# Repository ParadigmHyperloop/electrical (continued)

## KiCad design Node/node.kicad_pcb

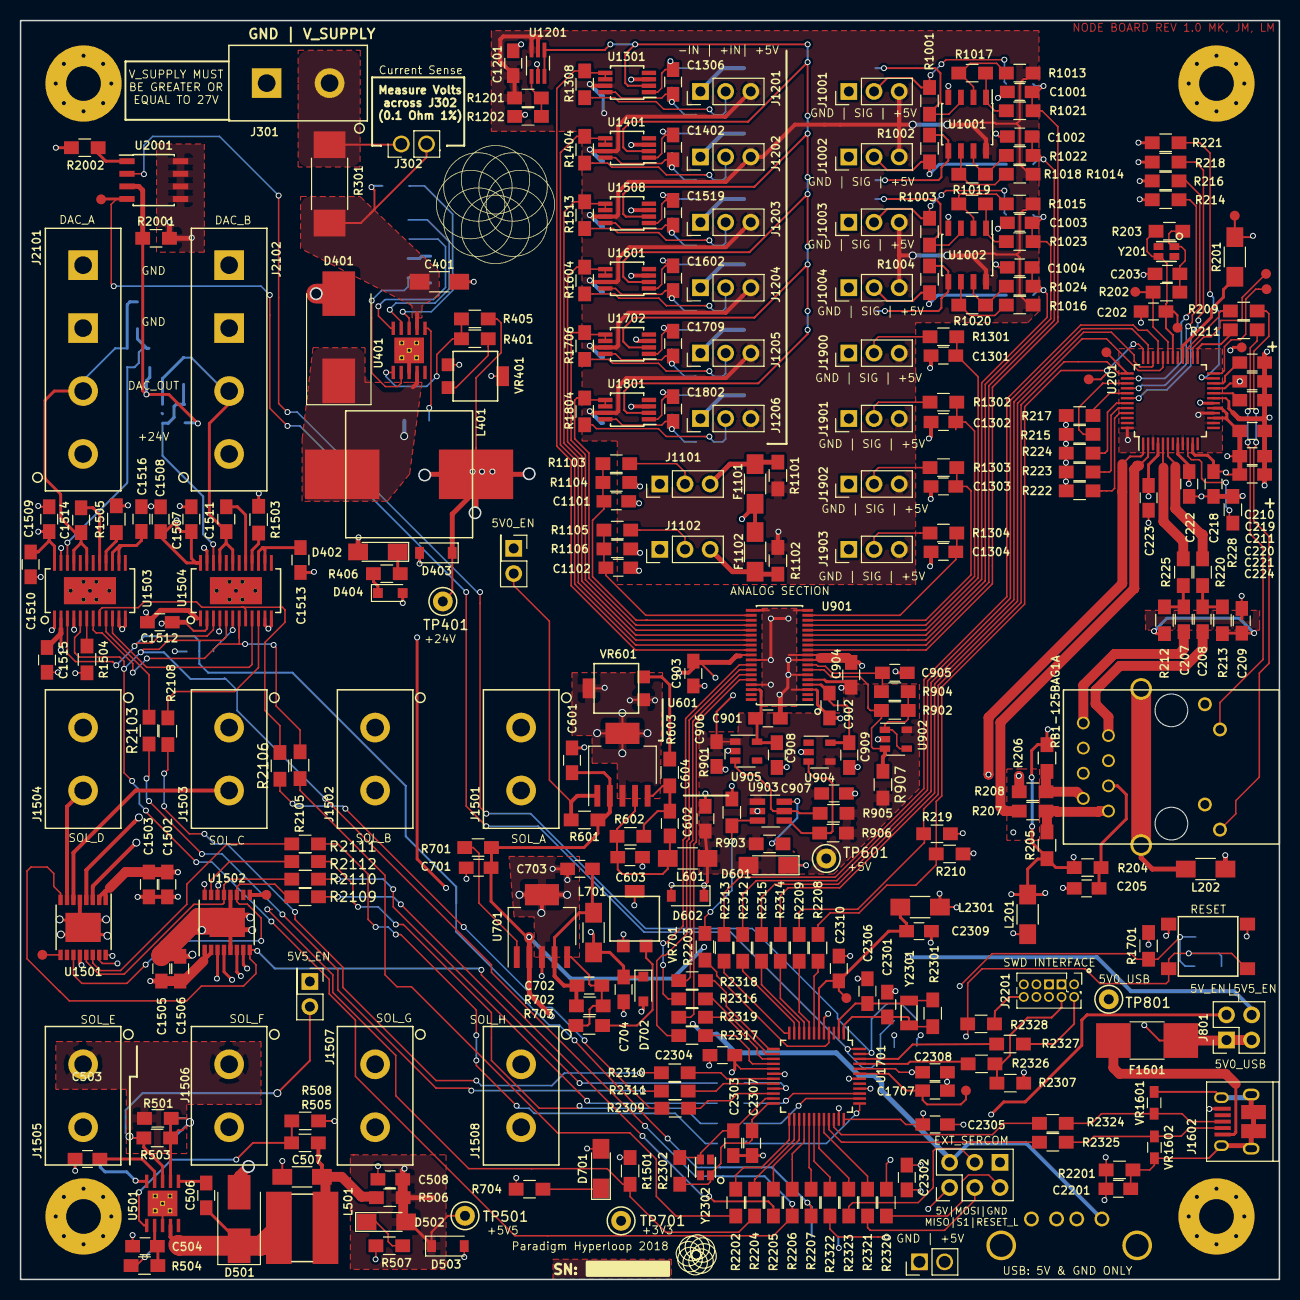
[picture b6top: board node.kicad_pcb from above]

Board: 4 copper layers, 127.0 x 127.0 mm, 399 parts (0 on the bottom side), 258 nets.

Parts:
C202, C203: 18pF; C_0805_HandSoldering
C205, C405, C506: 100nF; C_0805_HandSoldering
C207, C208: 6.8nF; C_0805_HandSoldering
C209, C210: 10nF; C_0805_HandSoldering
C211: 4.7uF; C_0805_HandSoldering
C218, C902, C2302, C2309: 10uF; C_0805_HandSoldering
C219, C220, C221, C222, C223, C224, C909, C1305, C1307, C1308, C1401, C1403, C1404, C1502, C1505, C1507, C1508, C1509, C1510, C1512, C1513, C1515, C1516, C1518, C1520, C1521, C1601, C1603, C1604, C1702, C1708, C1710, C1711, C1801, C1803, C1804, C2304, C2305, C2308, C2310: 0.1uF; C_0805_HandSoldering
C401: 2.2uF; C_1206_HandSoldering
C402, C503: 2.7nF; C_0805_HandSoldering
C403: 82pF; C_0805_HandSoldering
C404: 2.4nF; C_0805_HandSoldering
C406, C407: 22uF; C_0805_HandSoldering
C501, C502: 2.2uF; C_0805_HandSoldering
C504: 12nF; C_0805_HandSoldering
C505: 10pF; C_0805_HandSoldering
C507: 47uF; C_1206_HandSoldering
C508, C601, C603, C701, C703, C901, C903, C904, C906, C907, C908, C1201, C1306, C1402, C1519, C1602, C1707, C1709, C1802: 1uF; C_0805_HandSoldering
C602, C702, C2303, C2307: 15pF; C_0805_HandSoldering
C604, C704, C1001, C1002, C1003, C1004, C1101, C1102, C1301, C1302, C1303, C1304: C; C_0805_HandSoldering
C905: 150pF; C_0805_HandSoldering
C1503, C1506: 100uF; C_0805_HandSoldering
C1511, C1514: NOSTUFF; C_0805_HandSoldering
C2201: 4.5nF; C_0805_HandSoldering
C2301, C2306: 22pF; C_0805_HandSoldering
D401: DIODESCH; D_SMC_Handsoldering
D402, D502, D601, D701: GRN; LED_1206_HandSoldering
D403: 25V; D_SOD-123
D404: 20V; D_SOD-323_HandSoldering
D501: DIODESCH; D_SMB_Handsoldering
D503, D602: 6V; D_SOD-123
D702: 3.6V; D_SOD-323_HandSoldering
F1101, F1102: Fuse; R_1206_HandSoldering
F1601: Fuse; R_1812_HandSoldering
J201: RB1-125BAG1A; WIZNET_RB1-125BAG1A
J301, J1501, J1502, J1503, J1504, J1505, J1506, J1507, J1508: CONN_01X02; Molex_2pin_power_0010844022
J302, J303: CONN_01X02; Pin_Header_Straight_1x02_Pitch2.54mm
J801: Conn_02x02_Odd_Even; Pin_Header_Straight_2x02_Pitch2.54mm
J802, J803: Conn_02x01; Pin_Header_Straight_2x01_Pitch2.54mm
J1001, J1002, J1003, J1004, J1101, J1102, J1201, J1202, J1203, J1204, J1205, J1206, J1900, J1901, J1902, J1903: Conn_01x03; TE_3_pos_header_640456-3
J1601: Conn_02x03_Odd_Even; Pin_Header_Straight_2x03_Pitch2.54mm
J1602: USB_B_Micro; USB_Micro-B_10103594-0001LF
J2101, J2102: CONN_01X04; Molex_4pin_power_10-84-4042
J2201: Conn_02x05_Odd_Even; Pin_Header_Straight_2x05_Pitch1.27mm
L201, L202, L2301: Ferrite_Bead_Small; R_1206_HandSoldering
L401: 33uH; Wurth_inductor_7443551331
L501: 33uH; Bourns_33uH_inductor_SRR6028-330Y
L601, L701: INDUCTOR_SMALL; R_1206_HandSoldering
MK301, MK302, MK303, MK304: Mounting_Hole_PAD; MountingHole_M3x0.5_3.5mm_hole
P2101: USB_B; USB_A
R201: 0; R_1206_HandSoldering
R202, R403, R501, R506, R902, R1001, R1002, R1003, R1004, R1009, R1010, R1011, R1012, R1021, R1022, R1023, R1024, R1101, R1102, R1301, R1302, R1303, R1304, R1308, R1404, R1502, R1503, R1504, R1505, R1507, R1508, R1513, R1604, R1706, R1804, R2001, R2103, R2105, R2106, R2108, R2109, R2110, R2111, R2112, R2202, R2203, R2204, R2205, R2206, R2207, R2208, R2209, R2309, R2310, R2311, R2312, R2313, R2314, R2315, R2316, R2317, R2318, R2319, R2320, R2321, R2322, R2323, R2324, R2325, R2326, R2327, R2328, R2329, R2330, R2331, R2332: 0; R_0805_HandSoldering
R203, R1305, R1401, R1510, R1601, R1703, R1801, R2201: 1M; R_0805_HandSoldering
R204: 10; R_0805_HandSoldering
R205, R206, R212, R213: 49.9; R_0805_HandSoldering
R207, R208, R220, R225: 33; R_0805_HandSoldering
R209, R211, R704, R1702: 330; R_0805_HandSoldering
R210, R214, R215, R216, R217, R218, R219, R221, R222, R223, R224, R1701: 10K; R_0805_HandSoldering
R228: 12.4K; R_0805_HandSoldering
R301: 100m; R_2512_HandSoldering
R401: 11.5k; R_0805_HandSoldering
R402: 210k; R_0805_HandSoldering
R404: 27.4k; R_0805_HandSoldering
R405: 348k; R_0805_HandSoldering
R406: 698; R_0805_HandSoldering
R502: 124k; R_0805_HandSoldering
R503, R601, R701, R1017, R1018, R1019, R1020, R1501, R1506: 10k; R_0805_HandSoldering
R504: 17.4k; R_0805_HandSoldering
R505: 66.5k; R_0805_HandSoldering
R507: 1.4k; R_0805_HandSoldering
R508: 11.3k; R_0805_HandSoldering
R602: 93.1k; R_0805_HandSoldering
R603, R703: 29.4k; R_0805_HandSoldering
R604: 1.2k; R_0805_HandSoldering
R702: 51k; R_0805_HandSoldering
R901, R1202: 5k; R_0805_HandSoldering
R903, R905, R906: 100k; R_0805_HandSoldering
R904: 100; R_0805_HandSoldering
R907: 50K; R_0805_HandSoldering
R1005, R1006, R1007, R1008: 250; R_0805_HandSoldering
R1013, R1014, R1015, R1016: 40k; R_0805_HandSoldering
R1103, R1105: 82k; R_0805_HandSoldering
R1104, R1106: 20k; R_0805_HandSoldering
R1201: 45k; R_0805_HandSoldering
R1306, R1307, R1402, R1403, R1511, R1512, R1602, R1603, R1704, R1705, R1802, R1803, R2002: 150; R_0805_HandSoldering
R2003, R2004: 15k; R_0805_HandSoldering
R2301, R2302: NOSTUFF; R_0805_HandSoldering
R2307: 1k; R_0805_HandSoldering
SW1701: SW_Push; C&K_switch_PTS645SM43SMTR92
TP201, TP202, TP203, TP204, TP205, TP206, TP207, TP208, TP2001, TP2201, TP2301: Conn_01x01; Testpoint_circle_0.5mm
TP401, TP501, TP601, TP701, TP801: Test_Point; Test_Point_Keystone_5000-5004_Miniature
TP2101, TP2102: CONN_01X01; Testpoint_circle_0.5mm
U201: W5500; LQFP-48_7x7mm_Pitch0.5mm
U401, U501: TPS54361; TI_buckreg_TPS54361DPRR
U601, U701: TPS795; SOT-223-6
U901: ADS7953; TSSOP-38_4.4x9.7mm_Pitch0.5mm
U902: OPA192; SOT-23-5
U903: LM3880; SOT-23-6_Handsoldering
U904: LM4132; SOT-23-5
U905: TLV71333; SOT-23-5
U1001, U1002: LM358; SOIC-8_3.9x4.9mm_Pitch1.27mm
U1201: LMV601; SOT-363_SC-70-6_Handsoldering
U1301, U1401, U1508, U1601, U1702, U1801: AD849X; MSOP-8_3x3mm_Pitch0.65mm
U1501, U1502: DRV8806; TSSOP-16-1EP_4.4x5mm_Pitch0.65mm
U1503, U1504: DAC7760; HTSSOP-24_7.8x4.4mm_Pitch0.65mm_ThermalPad
U1505, U1506: OPA172; SOT-23-5
U1701: IC_MICROCHIP_SAMD21G18A-A; TQFP-48_7x7mm_Pitch0.5mm
U2001: BTS4300SGA; SOIC-8_3.9x4.9mm_Pitch1.27mm
VR401, VR601, VR701: 1k; TT_1k_potentiometer_23BR1KLFTR
VR1601, VR1602: VR; R_0603_HandSoldering
Y201, Y2302: 25MHz; Murata_25MHz_XTAL_XRCGB25M000F3M00R0
Y2301: 32.768kHz; TXC_32kHz_XTAL_9HT10-32.768KBZY-T

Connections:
3V3A_SAMD: C2309.1, C2310.1, L2301.1, TP2301.1, U1701.6
3V3A_W5500: C218.1, C219.1, C220.1, C221.1, C222.1, C223.1, C224.1, J201.L1, J201.L3, L201.2, R201.2, R204.2, R205.1, R206.1, R210.2, R219.2, TP208.1, U201.4, U201.8, U201.11, U201.15, U201.17, U201.21
+3V3: C704.1, C1512.2, C1515.2, C2302.1, C2304.1, C2305.1, C2308.1, D701.2, D702.1, J2201.1, L201.1, L701.2, L2301.2, R1501.1, R1506.1, R1701.2, R2003.1, R2004.1, R2307.2, TP701.1, U1503.2, U1504.2, U1701.17, U1701.36, U1701.44
+5V: C604.1, C903.1, C904.1, C906.1, C907.1, C1201.2, C1308.2, C1404.2, C1521.2, C1604.2, C1711.2, C1804.2, D601.2, D602.1, J303.2, J801.2, J1001.3, J1002.3, J1003.3, J1004.3, J1201.3, J1202.3, J1203.3, J1204.3, J1205.3, J1206.3, J1601.2, J1900.3, J1901.3, J1902.3, J1903.3, L601.2, P2101.1, R903.1, R905.1, R906.1, R907.1, R1013.2, R1014.2, R1015.2, R1016.2, R1101.1, R1102.1, R1201.1, TP601.1, U901.5, U901.29, U902.5, U903.1, U904.4, U905.1, U1001.8, U1002.8, U1201.5, U1201.6, U1301.7, U1401.7, U1508.7, U1601.7, U1702.7, U1801.7
+24V: C406.1, C407.1, C1502.2, C1503.2, C1505.2, C1506.2, D402.2, D403.1, F1101.1, F1102.1, J1501.1, J1502.1, J1503.1, J1504.1, J1505.1, J1506.1, J1507.1, J1508.1, J2101.1, J2102.1, L401.2, R405.1, R501.2, R2001.2, TP401.1, U1501.1, U1501.2, U1502.1, U1502.2, U2001.5, U2001.6, U2001.7, U2001.8
/Actuator Interface/24V0_DAC: C1507.2, C1508.2, C1509.2, C1510.2, R2001.1, U1503.24, U1504.24, U1505.5, U1506.5, U2001.3
/Actuator Interface/DAC1_CLR_SEL: R1504.2, U1503.6
/Actuator Interface/DAC1_DATAIN: R2103.2, U1503.9
/Actuator Interface/DAC1_DATAOUT: U1503.10, U1504.9
/Actuator Interface/DAC1_DVDD_EN_L: R1505.2, U1503.16
/Actuator Interface/DAC1_VIOUT: C1514.1, J2101.2, R1508.1, U1503.19, U1503.21, U1505.3
/Actuator Interface/DAC1_VREF: C1516.2, U1503.14, U1503.15
/Actuator Interface/DAC1_VSENSE+: R1508.2, U1503.22, U1505.1, U1505.4
/Actuator Interface/DAC2_CLR_SEL: R1502.2, U1504.6
/Actuator Interface/DAC2_DATAOUT: R2108.2, U1504.10
/Actuator Interface/DAC2_DVDD_EN_L: R1503.2, U1504.16
/Actuator Interface/DAC2_VIOUT: C1511.1, J2102.2, R1507.1, U1504.19, U1504.21, U1506.3
/Actuator Interface/DAC2_VREF: C1513.2, U1504.14, U1504.15
/Actuator Interface/DAC2_VSENSE+: R1507.2, U1504.22, U1506.1, U1506.4
/Actuator Interface/DAC_ALARM_L: R1506.2, R2207.2, U1503.3, U1504.3
/Actuator Interface/DAC_CLR: R2206.2, U1503.5, U1504.5
/Actuator Interface/DAC_CS: R2105.2, U1503.7, U1504.7
/Actuator Interface/DAC_SCLK: R2106.2, U1503.8, U1504.8
/Actuator Interface/Q0: R2109.1, R2109.2, R2329.2, U1501.11, U1502.11
/Actuator Interface/Q1: R2110.1, R2330.2
/Actuator Interface/Q2: R2111.1, R2331.2
/Actuator Interface/Q3: R2112.1, R2332.2
/Actuator Interface/SOL1_DATAIN: R2111.2, U1501.14
/Actuator Interface/SOL1_DATAOUT: U1501.15, U1502.14
/Actuator Interface/SOL1_OUT1: J1501.2, U1501.3
/Actuator Interface/SOL1_OUT2: J1502.2, U1501.4
/Actuator Interface/SOL1_OUT3: J1503.2, U1501.6
/Actuator Interface/SOL1_OUT4: J1504.2, U1501.7
/Actuator Interface/SOL1_RST: TP2102.1, U1501.9
/Actuator Interface/SOL2_DATAOUT: R2112.2, U1502.15
/Actuator Interface/SOL2_OUT1: J1505.2, U1502.3
/Actuator Interface/SOL2_OUT2: J1506.2, U1502.4
/Actuator Interface/SOL2_OUT3: J1507.2, U1502.6
/Actuator Interface/SOL2_OUT4: J1508.2, U1502.7
/Actuator Interface/SOL2_RST: TP2101.1, U1502.9
/Actuator Interface/SOL_DAC_C0: R1501.2, R2204.2, U1501.16, U1502.16
/Actuator Interface/SOL_DAC_C1: R2205.2, U1501.8, U1502.8
/Actuator Interface/SOL_DAC_CS2: R2105.1, R2202.2
/Actuator Interface/SOL_DAC_MISO: R2108.1, R2310.2
/Actuator Interface/SOL_DAC_MOSI: R2103.1, R2311.2
/Actuator Interface/SOL_DAC_S1: R2106.1, R2309.2
/Actuator Interface/SOL_SCLK: R2110.2, U1501.13, U1502.13
/Microcontroller/ADC_CS: R2316.2, U901.31
/Microcontroller/ADC_MISO: R2318.2, U901.33
/Microcontroller/ADC_MOSI: R2319.2, U901.34
/Microcontroller/ADC_S1: R2317.2, U901.32
/Microcontroller/EXT_RESET_L: R1702.2, R2320.1, R2328.1, SW1701.2
/Microcontroller/ISP_MISO: J1601.1, R2322.2
/Microcontroller/ISP_MOSI: J1601.4, R2323.2
/Microcontroller/ISP_RESET_L: J1601.5, R2320.2
/Microcontroller/ISP_S1: J1601.3, R2321.2
/Microcontroller/NETW_C0: R210.1, R2208.2, TP205.1, U201.36
/Microcontroller/NETW_C1: R219.1, R2209.2, TP204.1, U201.37
/Microcontroller/NETW_CS: R2314.2, U201.32
/Microcontroller/NETW_MISO: R2315.2, U201.34
/Microcontroller/NETW_MOSI: R2312.2, U201.35
/Microcontroller/NETW_S1: R2313.2, U201.33
/Microcontroller/PA03: R2203.1, U1701.4
/Microcontroller/PA04: R2314.1, U1701.9
/Microcontroller/PA05: R2315.1, U1701.10
/Microcontroller/PA06: R2312.1, U1701.11
/Microcontroller/PA07: R2313.1, U1701.12
/Microcontroller/PA08: R2318.1, U1701.13
/Microcontroller/PA09: R2316.1, U1701.14
/Microcontroller/PA10: R2319.1, U1701.15
/Microcontroller/PA11: R2317.1, U1701.16
/Microcontroller/PA12: R2329.1, U1701.21
/Microcontroller/PA13: R2309.1, U1701.22
/Microcontroller/PA14: C2303.1, R2302.2, U1701.23, Y2302.2
/Microcontroller/PA15: C2307.1, R2302.1, U1701.24, Y2302.1
/Microcontroller/PA16: R2202.1, U1701.25
/Microcontroller/PA17: R2204.1, U1701.26
/Microcontroller/PA18: R2205.1, U1701.27
/Microcontroller/PA19: R2206.1, U1701.28
/Microcontroller/PA20: R2207.1, U1701.29
/Microcontroller/PA21: R2322.1, U1701.30
/Microcontroller/PA22: R2323.1, U1701.31
/Microcontroller/PA23: R2321.1, U1701.32
/Microcontroller/PA27: R2330.1, U1701.39
/Microcontroller/PA30: R2326.1, U1701.45
/Microcontroller/PA31: R2327.1, U1701.46
/Microcontroller/PB02: R2003.2, U1701.47, U2001.2
/Microcontroller/PB03: R2004.2, TP2001.1, U1701.48, U2001.4
/Microcontroller/PB08: R2208.1, U1701.7
/Microcontroller/PB09: R2209.1, U1701.8
/Microcontroller/PB10: R2310.1, U1701.19
/Microcontroller/PB11: R2311.1, U1701.20
/Microcontroller/PB12: R2331.1, U1701.37
/Microcontroller/PB13: R2332.1, U1701.38
/Microcontroller/RESET_L: C1702.1, R1701.1, R1702.1, U1701.40
/Microcontroller/SWDCLK: J2201.4, R2307.1, R2326.2
/Microcontroller/SWDIO: J2201.2, R2327.2
/Microcontroller/SWD_RESET_L: J2201.10, R2328.2
/Microcontroller/USB_D+: J1602.3, R2324.2, VR1601.1
/Microcontroller/USB_D-: J1602.2, R2325.2, VR1602.1
/Microcontroller/USB_R_D+: R2324.1, U1701.34
/Microcontroller/USB_R_D-: R2325.1, U1701.33
/Microcontroller/VDDCORE_1V2: C1707.2, TP2201.1, U1701.43
/Microcontroller/XTAL32K_IN: C2301.1, R2301.2, U1701.1, Y2301.1
/Microcontroller/XTAL32K_OUT: C2306.1, R2301.1, U1701.2, Y2301.2
/Network_Interface/1V2_VBG_NC: TP207.1, U201.18
/Network_Interface/1V20: C210.1, U201.22
/Network_Interface/3V3D_W5500: R201.1, U201.28
/Network_Interface/ACT_LED: R209.2, U201.27
/Network_Interface/ACT_LED_R: J201.L4, R209.1
/Network_Interface/DUP_LED_NC: TP201.1, U201.26
/Network_Interface/LINK_LED: R211.1, U201.25
/Network_Interface/LINK_LED_R: J201.L2, R211.2
/Network_Interface/PMODE0: R222.2, U201.45
/Network_Interface/PMODE1: R223.2, U201.44
/Network_Interface/PMODE2: R224.2, U201.43
/Network_Interface/REF_CAP: C211.1, U201.20
/Network_Interface/REF_RES: R228.2, U201.10
/Network_Interface/RSVD0: R221.2, U201.23
/Network_Interface/RSVD1: R214.1, U201.38
/Network_Interface/RSVD2: R215.1, U201.39
/Network_Interface/RSVD3: R216.1, U201.40
/Network_Interface/RSVD4: R217.1, U201.41
/Network_Interface/RSVD5: R218.1, U201.42
/Network_Interface/RX_C_N: C207.2, J201.R8
/Network_Interface/RX_C_P: C208.2, J201.R7
/Network_Interface/RX_N: R225.2, U201.5
/Network_Interface/RX_P: R220.2, U201.6
/Network_Interface/SPD_LED_NC: TP206.1, U201.24
/Network_Interface/TCT_RCT: C205.1, J201.R3, R204.1
/Network_Interface/TX_N: R208.2, U201.1
/Network_Interface/TX_P: R207.2, U201.2
/Network_Interface/TX_R_N: J201.R2, R206.2, R208.1
/Network_Interface/TX_R_P: J201.R1, R205.2, R207.1
/Network_Interface/XTAL_IN: C202.2, R203.2, TP203.1, U201.30, Y201.2
/Network_Interface/XTAL_OUT: R202.2, TP202.1, U201.31
/Power/3.3V (Clean) Supply/3V3_UNFILT: C702.1, C703.1, L701.1, R702.1, U701.4
/Power/3.3V (Clean) Supply/5V5: C508.1, C601.1, C701.1, D502.2, D503.1, J801.4, R506.1, R601.1, R701.1, TP501.1, U601.2, U701.2
/Power/5.5V (Noisy) Supply/5V5_UNFILT: C507.1, L501.2, R505.1, R506.2
/Power/5.5V (Noisy) Supply/24V0_R: C501.1, C502.1, R501.1, R503.2, U501.2
/Power/5.5V (Noisy) Supply/COMP: C504.1, R504.1, U501.7
/Power/5.5V (Noisy) Supply/ENABLE: J803.2, R503.1, U501.3
/Power/5.5V (Noisy) Supply/FB: R505.2, R508.1, U501.6
/Power/5.5V (Noisy) Supply/RT: R502.1, U501.5
/Power/5.5V (Noisy) Supply/SS: C503.1, U501.4
/Power/5.5V (Noisy) Supply/SW: C506.1, D501.1, L501.1, U501.9
/Power/5V0_USB: F1601.2, J801.1, J801.3, TP801.1
/Power/5V (Clean) Supply/5V0_UNFILT: C602.1, C603.1, L601.1, R602.1, U601.4
/Power/5V (Clean) Supply/ENABLE: J802.2, R601.2, U601.1
/Power/ISENSE_N: C401.1, J302.2, R301.1, R403.2, U401.2
/Power/ISENSE_P: J301.1, J302.1, R301.2
/Power/Motor Supply/COMP: C403.1, R404.1, U401.7
/Power/Motor Supply/EN: R403.1, U401.3
/Power/Motor Supply/FB: R401.1, R405.2, U401.6
/Power/Motor Supply/RT: R402.1, U401.5
/Power/Motor Supply/SS: C402.1, U401.4
/Power/Motor Supply/SW: C405.1, D401.1, L401.1, U401.9
/Sensors/ADC/3V3_EN: R905.2, U903.5, U905.3
/Sensors/ADC/ADC_CH0: R1308.1, U901.28, U1301.5, U1301.6
/Sensors/ADC/ADC_CH1: R1404.1, U901.27, U1401.5, U1401.6
/Sensors/ADC/ADC_CH2: R1513.1, U901.26, U1508.5, U1508.6
/Sensors/ADC/ADC_CH3: R1604.1, U901.25, U1601.5, U1601.6
/Sensors/ADC/ADC_CH4: R1706.1, U901.24, U1702.5, U1702.6
/Sensors/ADC/ADC_CH5: R1804.1, U901.23, U1801.5, U1801.6
/Sensors/ADC/ADC_CH6: C1101.1, R1103.2, R1104.1, U901.22
/Sensors/ADC/ADC_CH7: C1102.1, R1105.2, R1106.1, U901.21
/Sensors/ADC/ADC_CH8: C1304.1, R1304.1, U901.18
/Sensors/ADC/ADC_CH9: C1303.1, R1303.1, U901.17
/Sensors/ADC/ADC_CH10: C1302.1, R1302.1, U901.16
/Sensors/ADC/ADC_CH11: C1301.1, R1301.1, U901.15
/Sensors/ADC/ADC_CH12: C1004.1, R1012.1, R1024.1, U901.14
/Sensors/ADC/ADC_CH13: C1003.1, R1011.1, R1023.1, U901.13
/Sensors/ADC/ADC_CH14: C1002.1, R1010.1, R1022.1, U901.12
/Sensors/ADC/ADC_CH15: C1001.1, R1009.1, R1021.1, U901.11
/Sensors/ADC/AINP: C905.1, R904.1, U901.8
/Sensors/ADC/MXO: R902.1, R907.2, U901.7, U902.3
/Sensors/ADC/POWER_SEQ_ADC: R901.1, R2203.2, U903.3
/Sensors/ADC/TC_to_Volt/tc_to_v_0/+IN: J1201.2, R1307.2, R1308.2
/Sensors/ADC/TC_to_Volt/tc_to_v_0/-IN: J1201.1, R1305.2, R1306.2
/Sensors/ADC/TC_to_Volt/tc_to_v_1/+IN: J1202.2, R1403.2, R1404.2
/Sensors/ADC/TC_to_Volt/tc_to_v_1/-IN: J1202.1, R1401.2, R1402.2
/Sensors/ADC/TC_to_Volt/tc_to_v_2/+IN: J1203.2, R1512.2, R1513.2
/Sensors/ADC/TC_to_Volt/tc_to_v_2/-IN: J1203.1, R1510.2, R1511.2
/Sensors/ADC/TC_to_Volt/tc_to_v_3/+IN: J1204.2, R1603.2, R1604.2
/Sensors/ADC/TC_to_Volt/tc_to_v_3/-IN: J1204.1, R1601.2, R1602.2
/Sensors/ADC/TC_to_Volt/tc_to_v_4/+IN: J1205.2, R1705.2, R1706.2
/Sensors/ADC/TC_to_Volt/tc_to_v_4/-IN: J1205.1, R1703.2, R1704.2
/Sensors/ADC/TC_to_Volt/tc_to_v_5/+IN: J1206.2, R1803.2, R1804.2
/Sensors/ADC/TC_to_Volt/tc_to_v_5/-IN: J1206.1, R1801.2, R1802.2
/Sensors/ADC/TC_to_Volt/tc_vref: U1201.3, U1201.4, U1301.2, U1401.2, U1508.2, U1601.2, U1702.2, U1801.2
/Sensors/ADC/VREF_EN: R906.2, U903.4, U904.3
/USB Interface/USB_SHLD: C2201.1, J1602.6, R2201.1, VR1601.2, VR1602.2
ADC_2V5_REF: C902.1, C909.2, U901.4, U904.5
ADC_3V3: C901.1, C908.1, U901.36, U905.5
GND: C202.1, C203.1, C205.2, C209.2, C210.2, C211.2, C218.2, C219.2, C220.2, C221.2, C222.2, C223.2, C224.2, C401.2, C402.2, C403.2, C404.2, C406.2, C407.2, C501.2, C502.2, C503.2, C504.2, C505.2, C507.2, C508.2, C601.2, C603.2, C604.2, C701.2, C703.2, C704.2, C901.2, C902.2, C903.2, C904.2, C905.2, C906.2, C907.2, C908.2, C909.1, C1001.2, C1002.2, C1003.2, C1004.2, C1101.2, C1102.2, C1201.1, C1301.2, C1302.2, C1303.2, C1304.2, C1305.1, C1307.2, C1308.1, C1401.1, C1403.2, C1404.1, C1502.1, C1503.1, C1505.1, C1506.1, C1507.1, C1508.1, C1509.1, C1510.1, C1512.1, C1513.1, C1515.1, C1516.1, C1518.1, C1520.2, C1521.1, C1601.1, C1603.2, C1604.1, C1702.2, C1707.1, C1708.1, C1710.2, C1711.1, C1801.1, C1803.2, C1804.1, C2201.2, C2301.2, C2302.2, C2303.2, C2304.2, C2305.2, C2306.2, C2307.2, C2308.2, C2309.2, C2310.2, D401.2, D403.2, D404.2, D501.2, D503.2, D602.2, D702.2, J301.2, J303.1, J802.1, J803.1, J1001.1, J1002.1, J1003.1, J1004.1, J1101.1, J1102.1, J1601.6, J1602.5, J1900.1, J1901.1, J1902.1, J1903.1, J2101.3, J2101.4, J2102.3, J2102.4, J2201.3, J2201.5, L202.1, MK301.1, MK302.1, MK303.1, MK304.1, P2101.4, P2101.5, R214.2, R215.2, R216.2, R217.2, R218.2, R221.1, R222.1, R223.1, R224.1, R228.1, R402.2, R502.2, R507.2, R508.2, R604.2, R704.2, R901.2, R1005.2, R1006.2, R1007.2, R1008.2, R1104.2, R1106.2, R1202.2, R1305.1, R1401.1, R1502.1, R1503.1, R1504.1, R1505.1, R1510.1, R1601.1, R1703.1, R1801.1, R2002.2, R2201.2, SW1701.1, U201.3, U201.9, U201.14, U201.16, U201.19, U201.29, U201.48, U401.8, U401.11, U501.8, U501.11, U601.3, U601.6, U701.3, U701.6, U901.3, U901.6, U901.9, U901.10, U901.19, U901.20, U901.30, U901.35, U902.2, U903.2, U904.2, U905.2, U1001.4, U1002.4, U1201.2, U1301.3, U1401.3, U1501.5, U1501.12, U1501.17, U1502.5, U1502.12, U1502.17, U1503.1, U1503.4, U1503.11, U1503.12, U1503.23, U1504.1, U1504.4, U1504.11, U1504.12, U1504.23, U1505.2, U1506.2, U1508.3, U1601.3, U1701.5, U1701.18, U1701.35, U1701.42, U1702.3, U1801.3, VR401.2, VR401.3, VR601.2, VR601.3, VR701.2, VR701.3
unnamed: C203.2, R202.1, R203.1, Y201.1
unnamed: C207.1, R212.1, R225.1
unnamed: C208.1, R213.1, R220.1
unnamed: C209.1, R212.2, R213.2
unnamed: C404.1, R404.2
unnamed: C405.2, U401.1
unnamed: C505.1, R504.2
unnamed: C506.2, U501.1
unnamed: C602.2, R602.2, R603.1, U601.5
unnamed: C702.2, R702.2, R703.1, U701.5
unnamed: C1305.2, C1306.2, R1306.1, U1301.1
unnamed: C1306.1, C1307.1, R1307.1, U1301.8
unnamed: C1401.2, C1402.2, R1402.1, U1401.1
unnamed: C1402.1, C1403.1, R1403.1, U1401.8
unnamed: C1511.2, U1504.17
unnamed: C1514.2, U1503.17
unnamed: C1518.2, C1519.2, R1511.1, U1508.1
unnamed: C1519.1, C1520.1, R1512.1, U1508.8
unnamed: C1601.2, C1602.2, R1602.1, U1601.1
unnamed: C1602.1, C1603.1, R1603.1, U1601.8
unnamed: C1708.2, C1709.2, R1704.1, U1702.1
unnamed: C1709.1, C1710.1, R1705.1, U1702.8
unnamed: C1801.2, C1802.2, R1802.1, U1801.1
unnamed: C1802.1, C1803.1, R1803.1, U1801.8
unnamed: D402.1, R406.1
unnamed: D404.1, R406.2
unnamed: D502.1, R507.1
unnamed: D601.1, R604.1
unnamed: D701.1, R704.1
unnamed: F1101.2, J1101.3, R1101.2
unnamed: F1102.2, J1102.3, R1102.2
unnamed: F1601.1, J1602.1
unnamed: J201.SH, L202.2
unnamed: J1001.2, R1001.2, R1009.2
unnamed: J1002.2, R1002.2, R1010.2
unnamed: J1003.2, R1003.2, R1011.2
unnamed: J1004.2, R1004.2, R1012.2
unnamed: J1101.2, R1103.1
unnamed: J1102.2, R1105.1
unnamed: J1900.2, R1301.2
unnamed: J1901.2, R1302.2
unnamed: J1902.2, R1303.2
unnamed: J1903.2, R1304.2
unnamed: R401.2, VR401.1
unnamed: R603.2, VR601.1
unnamed: R701.2, U701.1
unnamed: R703.2, VR701.1
unnamed: R902.2, R904.2, U902.1, U902.4
unnamed: R903.2, U903.6
unnamed: R1001.1, R1005.1, U1001.3
unnamed: R1002.1, R1006.1, U1001.5
unnamed: R1003.1, R1007.1, U1002.3
unnamed: R1004.1, R1008.1, U1002.5
unnamed: R1013.1, R1017.2, U1001.2
unnamed: R1014.1, R1018.2, U1001.6
unnamed: R1015.1, R1019.2, U1002.2
unnamed: R1016.1, R1020.2, U1002.6
unnamed: R1017.1, R1021.2, U1001.1
unnamed: R1018.1, R1022.2, U1001.7
unnamed: R1019.1, R1023.2, U1002.1
unnamed: R1020.1, R1024.2, U1002.7
unnamed: R1201.2, R1202.1, U1201.1
unnamed: R2002.1, U2001.1

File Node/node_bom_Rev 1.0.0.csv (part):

Component,Description,Part,References,Value,Footprint,Quantity Per PCB,Datasheet,Digikey P/N,Mfg. Part Num,Vendor Part Num,Vendor Name,Mfg. Name,Vendor,Vendor P/N,MFG. P/N,Manufacturer,Package,MP,Stuffing,Tolerance,Manufacturer P/N,Mfr P/N
1,,C_small,C909 C1502 C1505 C1507 C1508 C1509 C1510 C1512 C1513 C1515 C1516,0.1uF,C_0805_HandSoldering,11,,,,,,,,,,,,,,,,
2,,C,C205 C219 C220 C221 C222 C223 C224 C1305 C1307 C1308 C1401 C1403 C1404 C1518 C1520 C1521 C1601 C1603 C1604 C1702 C1708 C1710 C1711 C1801 C1803 C1804 C2304 C2305 C2308 C2310,100nF,C_0805_HandSoldering,30,,311-1088-1-ND,,,,,,,,,,,,,,
3,,C_large,C405 C506,100nF,C_0805_HandSoldering,2,,,GMK212BJ104KGHT,587-3364-1-ND,Digi-Key,Taiyo Yuden,,,,,,,,,,
4,,C_small,C1503 C1506,100uF,C_0805_HandSoldering,2,,,,,,,,,,,,,,,,
5,,C,C209 C210,10nF,C_0805_HandSoldering,2,,,,,,,,,,,,,,,,
6,,C_large,C505,10pF,C_0805_HandSoldering,1,,,C0805C100K5GACTU,399-7975-1-ND,Digi-Key,Kemet,,,,,,,,,,
7,,C,C218 C2302 C2309,10uF,C_0805_HandSoldering,3,,,,,,,,,,,,,,,,
8,,C_small,C902,10uF,C_0805_HandSoldering,1,,,,,,,,,,,,,,,,
9,,C_large,C504,12nF,C_0805_HandSoldering,1,,,CL21B123KBANNNC,1276-2454-1-ND,Digi-Key,Samsung,,,,,,,,,,
10,,C_small,C905,150pF,C_0805_HandSoldering,1,,,,,,,,,,,,,,,,
11,,C,C2303 C2307,15pF,C_0805_HandSoldering,2,,,,,,,,,,,,,,,,
12,,C_large,C602 C702,15pF,C_0805_HandSoldering,2,,,CC0805JRNPO9BN150,311-1101-1-ND,Digi-Key,Yageo,,,,,,,,,,
13,,C,C202 C203,18pF,C_0805_HandSoldering,2,,,,,,,,,,,,,,,,
14,,C,C1201 C1306 C1402 C1519 C1602 C1707 C1709 C1802,1uF,C_0805_HandSoldering,8,,1276-1946-1-ND,,,,,,,,,,,,,,
15,,C_large,C508 C601 C603 C701 C703,1uF,C_0805_HandSoldering,5,,,GRT21BC81E105KE13L CC0805KRX5R7BB105,490-12351-1-ND 311-3427-1-ND,Digi-Key,Murata Yageo,,,,,,,,,,
16,,C_small,C901 C903 C904 C906 C907 C908,1uF,C_0805_HandSoldering,6,,,,,,,,,,,,,,,,
17,,C_large,C401,2.2uF,C_1206_HandSoldering,1,,,C3216X7S2A225K160AB,445-5207-1-ND,Digi-Key,TDK,,,,,,,,,,
18,,C_large,C501 C502,2.2uF,C_0805_HandSoldering,2,,,C2012X7R1H225K125AC,445-5968-1-ND,Digi-Key,TDK,,,,,,,,,,
19,,C_large,C404,2.4nF,C_0805_HandSoldering,1,,,GRM2165C1H242JA01D,490-1629-1-ND,Digi-Key,Murata,,,,,,,,,,
20,,C_large,C402 C503,2.7nF,C_0805_HandSoldering,2,,,CC0805KRX7R9BB272,311-1130-1-ND,Digi-Key,Yageo,,,,,,,,,,
21,,C,C2301 C2306,22pF,C_0805_HandSoldering,2,,,,,,,,,,,,,,,,
22,,C_large,C406 C407,22uF,C_0805_HandSoldering,2,,,C2012X5R1V226M125AC,445-14428-1-ND,Digi-Key,TDK,,,,,,,,,,
23,,C,C2201,4.5nF,C_0805_HandSoldering,1,,,,,,,,,,,,,,,,
24,,C,C211,4.7uF,C_0805_HandSoldering,1,,,,,,,,,,,,,,,,
25,,C_large,C507,47uF,C_1206_HandSoldering,1,,,CL31A476MPHNNNE,1276-3063-1-ND,Digi-Key,Samsung,,,,,,,,,,
26,,C,C207 C208,6.8nF,C_0805_HandSoldering,2,,,,,,,,,,,,,,,,
27,,C_large,C403,82pF,C_0805_HandSoldering,1,,,CL21C820JB61PNC,1276-2695-1-ND,Digi-Key,Samsung,,,,,,,,,,
28,,C,C1001 C1002 C1003 C1004 C1101 C1102 C1301 C1302 C1303 C1304,C,C_0805_HandSoldering,10,,,,,,,,,,,,,,,,
29,,C_large,C604 C704,C,C_0805_HandSoldering,2,,,,,,,,,,,,,,,,
30,,D_Zener_ALT,D404,20V,D_SOD-323_HandSoldering,1,,,MM3Z20VT1G,MM3Z20VT1GOSCT-ND,,ON Semi,,,,,,,,,,
31,,D_Zener_ALT,D403,25V,D_SOD-123,1,,,MMSZ4710T1G,MMSZ4710T1GOSCT-ND,Digi-Key,ON Semi,,,,,,,,,,
32,,D_Zener_ALT,D702,3.6V,D_SOD-323_HandSoldering,1,,,MM3Z3V6T1G,MM3Z3V6T1GOSCT-ND,Digi-Key,ON Semi,,,,,,,,,,
33,,D_Zener_ALT,D503 D602,6V,D_SOD-123,2,,,MMSZ5233B-TP,MMSZ5233B-TPMSCT-ND,Digi-Key,Micro,,,,,,,,,,
34,,DIODESCH,D401,DIODESCH,D_SMC_Handsoldering,1,,,B560C-13-F,B560C-FDICT-ND,Digi-Key,Diodes,,,,,,,,,,
35,,DIODESCH,D501,DIODESCH,D_SMB_Handsoldering,1,,,B140B-13-F,B140B-FDICT-ND,Digi-Key,Diodes,,,,,,,,,,
36,,LED,D402 D502 D601 D701,GRN,LED_1206_HandSoldering,4,,,APT3216LZGCK,754-1944-1-ND,Digi-Key,Kingbright,,,,,,,,,,
37,,Fuse,F1101 F1102,Fuse,R_1206_HandSoldering,2,,,C1Q 250,507-1073-1-ND,,Bel Fuse,,,,,,,,,,
38,,Fuse,F1601,Fuse,R_1812_HandSoldering,1,,,MF-MSMF050-2CT-ND,MF-MSMF050-2,,Bourns,,,,,,,,,,
39,"Generic connector, single row, 01x02",Conn_01x02,J301 J1501 J1502 J1503 J1504 J1505 J1506 J1507 J1508,CONN_01X02,Molex_2pin_power_0010844022,9,,,,,,,DigiKey,WM1263-ND,0010844022,"Molex, LLC Molex LLC",,,,,,
40,"Generic connector, single row, 01x02",Conn_01x02,J302 J303,CONN_01X02,Pin_Header_Straight_1x02_Pitch2.54mm,2,,,,,,,DigiKey,S7000-ND,PPTC021LFBN-RC,Sullins Conn. Solutions,,,,,,
41,"Generic connector, single row, 01x04",Conn_01x04,J1509 J1510,CONN_01X04,Molex_4pin_power_10-84-4042,2,,,,,,,DigiKey,WM1265-ND,10-84-4042,Molex Connector Corporation,,,,,,
42,"Generic connector, single row, 01x03",Conn_01x03,J1001 J1002 J1003 J1004 J1101 J1102 J1201 J1202 J1203 J1204 J1205 J1206 J1900 J1901 J1902 J1903,Conn_01x03,TE_3_pos_header_640456-3,16,,,640456-3,A19470-ND,,TE Connectivity,,,,,,,,,,
43,"Generic connector, double row, 02x01, this symbol is compatible with counter-clockwise, top-bottom and odd-even numbering schemes.",Conn_02x01,J802 J803,Conn_02x01,Pin_Header_Straight_2x01_Pitch2.54mm,2,,,,,,,DigiKey,952-2262-ND,M20-9990246,Harwin Inc,,,,,,
44,"Generic connector, double row, 02x02, odd/even pin numbering scheme (row 1 odd numbers, row 2 even numbers)",Conn_02x02_Odd_Even,J801,Conn_02x02_Odd_Even,Pin_Header_Straight_2x02_Pitch2.54mm,1,,,,,,,DigiKey,609-3242-ND,67997-404HLF,Amphenol FCI,,,,,,
45,"Generic connector, double row, 02x03, odd/even pin numbering scheme (row 1 odd numbers, row 2 even numbers)",Conn_02x03_Odd_Even,J1601,Conn_02x03_Odd_Even,Pin_Header_Straight_2x03_Pitch2.54mm,1,,,,,,,DigiKey,S9015E-03-ND,GRPB032VWVN-RC,Sullins Conn. Solutions,,,,,,
46,"Generic connector, double row, 02x05, odd/even pin numbering scheme (row 1 odd numbers, row 2 even numbers)",Conn_02x05_Odd_Even,J2201,Conn_02x05_Odd_Even,Pin_Header_Straight_2x05_Pitch1.27mm,1,,,,,,,DigiKey,609-3712-ND,20021111-00010T4LF,Amphenol FCI,,,,,,
47,,RB1-125BAG1A,J201,RB1-125BAG1A,WIZNET_RB1-125BAG1A,1,2.18 USD,,RB1-125BAG1A,,,WIZnet,,,,,HVQFN-36 NXP Semiconductors,RB1-125BAG1A,,,,
48,USB Micro Type B connector,USB_B_Micro,J1602,USB_B_Micro,USB_Micro-B_10103594-0001LF,1,,,609-4050-1-ND,10103594-0001LF,,Amphenol,,,,,,,,,,
49,,L_large,L401,33uH,Wurth_inductor_7443551331,1,,,7443551331,732-3881-1-ND,Digi-Key,Wurth Electronics,,,,,,,,,,
50,,L_large,L501,33uH,Bourns_33uH_inductor_SRR6028-330Y,1,,,SRR6028-330Y,SRR6028-330YCT-ND,Digi-Key,Bourns,,,,,,,,,,
51,,Ferrite_Bead_Small,L201 L202 L2301,Ferrite_Bead_Small,R_1206_HandSoldering,3,,,,,,,,,,,,,,,,
52,,L_small,L601 L701,INDUCTOR_SMALL,R_1206_HandSoldering,2,,,RC1206JR-070RL,311-0.0ERCT-ND,,Yageo,,,,,,,,,,
53,,R,R202 R1001 R1002 R1003 R1004 R1009 R1010 R1011 R1012 R1021 R1022 R1023 R1024 R1101 R1102 R1301 R1302 R1303 R1304 R1308 R1404 R1513 R1604 R1706 R1804 R2202 R2203 R2204 R2205 R2206 R2207 R2208 R2209 R2308 R2309 R2310 R2311 R2312 R2313 R2314 R2315 R2316 R2317 R2318 R2319 R2320 R2321 R2322 R2323 R2324 R2325 R2326 R2327 R2328,0,R_0805_HandSoldering,54,,,,,,,,,,,,,,,,
54,,R_large,R403 R501 R506 R1502 R1503 R1504 R1505 R1507 R1508 R2001 R2101 R2102 R2103 R2104 R2105 R2106 R2107 R2108,0,R_0805_HandSoldering,18,,,RC0805JR-070RL,311-0.0ARCT-ND,Digi-Key,Yageo,,,,,,,NOSTUFF,,,
55,,R,R201,0,R_1206_HandSoldering,1,,,,,,,,,,,,,,,,
56,,R_small,R902,0,R_0805_HandSoldering,1,,,,,,,,,,,,,,,,
57,,R_large,R604,1.2k,R_0805_HandSoldering,1,,,RC0805JR-071K2L,311-1.2KARCT-ND,Digi-Key,Yageo,,,,,,,,,,
58,,R_large,R507,1.4k,R_0805_HandSoldering,1,,,RC0805FR-071K4L,311-1.40KCRCT-ND,Digi-Key,Yageo,,,,,,,,,,
59,,R-RESCUE-node,R204,10,R_0805_HandSoldering,1,,,,,,,,,,,,,,1%,,
60,,R_small,R904,100,R_0805_HandSoldering,1,,,,,,,,,,,,,,,,
61,,R_large,R903 R905 R906,100k,R_0805_HandSoldering,3,,,,,,,DigiKey,,,,,,,,,
62,,R_large,R301,100m,R_2512_HandSoldering,1,,,CRA2512-FZ-R100ELF,CRA2512-FZ-R100ELFCT-ND,,Bourns,,,,,,,,,,
63,,R,R221 R1017 R1018 R1019 R1020 R1701,10K,R_0805_HandSoldering,6,,,,,,,,,,,,,,,,
64,,R-RESCUE-node,R210 R214 R215 R216 R217 R218 R219 R222 R223 R224,10K,R_0805_HandSoldering,10,,,,,,,,,,,,,,,,
65,,R_large,R503 R601 R701 R1501 R1506,10k,R_0805_HandSoldering,5,,,,,Digi-Key,,,,,,,,,,,
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
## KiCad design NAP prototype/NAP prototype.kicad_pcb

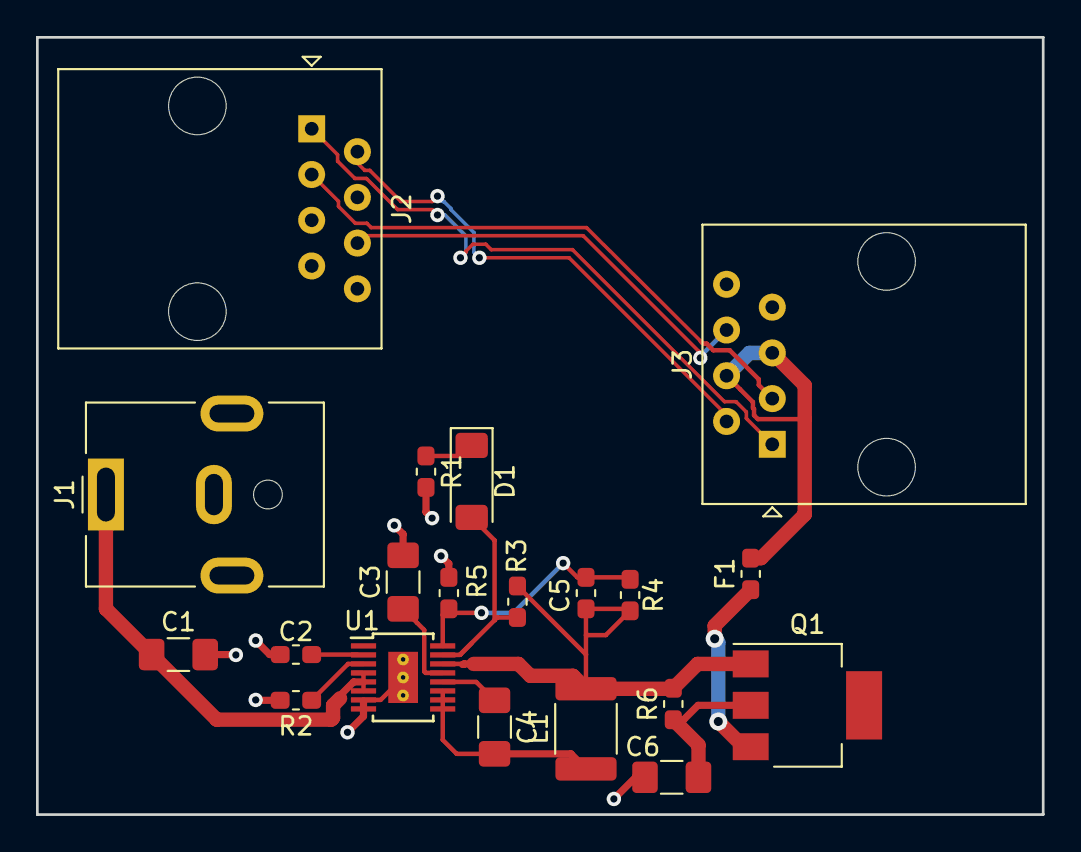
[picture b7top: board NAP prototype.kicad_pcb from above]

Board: 2 copper layers, 55.9 x 43.2 mm, 20 parts (0 on the bottom side), 18 nets.

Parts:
C1, C6: 4.7uF; C_1206_3216Metric_Pad1.42x1.75mm_HandSolder
C2: 10nF; C_0603_1608Metric_Pad1.05x0.95mm_HandSolder
C3: 1uF; C_1206_3216Metric_Pad1.42x1.75mm_HandSolder
C4: .1uF; C_1206_3216Metric_Pad1.42x1.75mm_HandSolder
C5: 10pF; C_0603_1608Metric_Pad1.05x0.95mm_HandSolder
D1: LED; D_1806_4516Metric
F1: Fuse; Fuse_0603_1608Metric_Pad1.05x0.95mm_HandSolder
J1: Jack-DC; BarrelJack_CUI_PJ-063AH_Horizontal
J2, J3: RJ45_LED_Shielded; RJ45_Amphenol_54602-x08_Horizontal
L1: 22uH; L_1812_4532Metric_Pad1.30x3.40mm_HandSolder
Q1: Q_NMOS_DGS; SOT-223
R1, R6: 10k; R_0603_1608Metric_Pad1.05x0.95mm_HandSolder
R2: 41.2k; R_0603_1608Metric_Pad1.05x0.95mm_HandSolder
R3: 100k; R_0603_1608Metric_Pad1.05x0.95mm_HandSolder
R4: 1M; R_0603_1608Metric_Pad1.05x0.95mm_HandSolder
R5: 88.7k; R_0603_1608Metric_Pad1.05x0.95mm_HandSolder
U1: LT8610; MSOP-16-1EP_3x4mm_P0.5mm_EP1.65x2.85mm_ThermalVias

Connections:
/RX+: J2.1, J3.1
/RX-: J2.2, J3.2
/TX+: J2.3, J3.3
/TX-: J2.6, J3.6
GND: C1.2, C2.2, C3.2, C6.2, J1.2, J3.7, J3.8, R1.2, R2.2, R5.1, U1.7, U1.8, U1.17
unnamed: C1.1, J1.1, U1.4, U1.5, U1.6
unnamed: C2.1, U1.2
unnamed: C3.1, U1.13
unnamed: C4.1, U1.12
unnamed: C4.2, L1.1, U1.9, U1.10, U1.11
unnamed: C5.1, R4.2, R5.2, U1.16
unnamed: C5.2, L1.2, Q1.1, R3.2, R4.1, R6.2, U1.14
unnamed: C6.1, Q1.2, R6.1
unnamed: D1.1, R1.1
unnamed: D1.2, R3.1, U1.15
unnamed: F1.1, Q1.3
unnamed: F1.2, J3.4, J3.5
unnamed: R2.1, U1.3
